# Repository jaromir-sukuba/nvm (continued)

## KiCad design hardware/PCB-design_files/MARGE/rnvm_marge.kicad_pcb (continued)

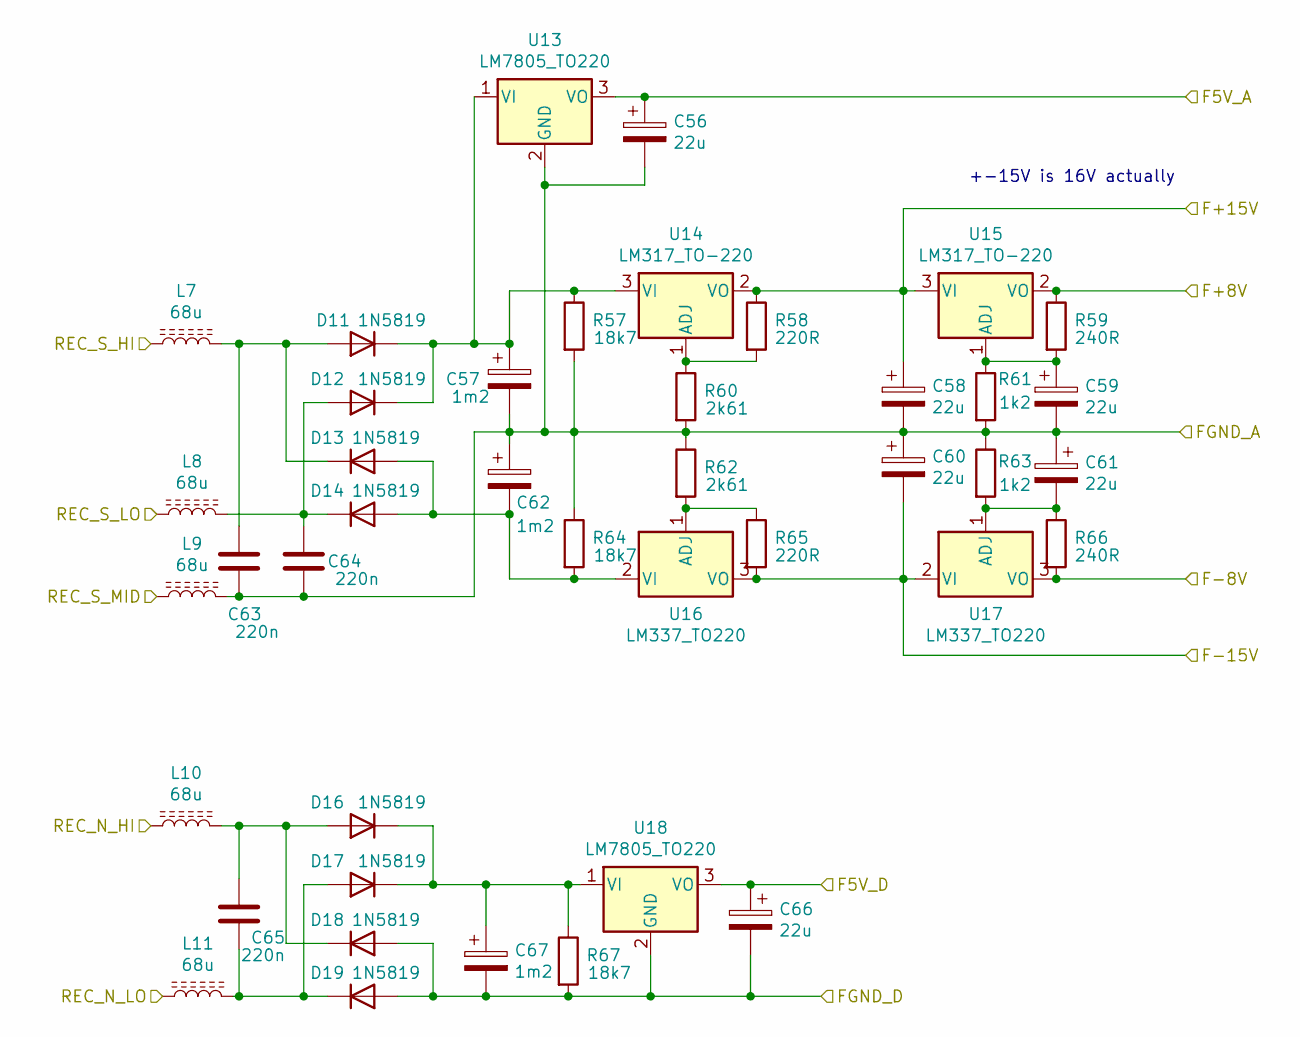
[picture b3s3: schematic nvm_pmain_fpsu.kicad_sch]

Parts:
C56, C58, C59, C60, C61, C66: 22u; CP_EIA-6032-28_Kemet-C_Pad2.25x2.35mm_HandSolder
C57, C62, C67: 1m2; CP_Radial_D12.5mm_P5.00mm
C63, C64, C65: 220n; C_0805_2012Metric_Pad1.18x1.45mm_HandSolder
D11, D12, D13, D14, D16, D17, D18, D19: 1N5819; D_MELF
L7, L8, L9, L10, L11: 68u; L_Bourns_SRN6045TA
R57, R64, R67: 18k7; R_MiniMELF_MMA-0204
R58, R65: 220R; R_MiniMELF_MMA-0204
R59, R66: 240R; R_MiniMELF_MMA-0204
R60, R62: 2k61; R_MiniMELF_MMA-0204
R61, R63: 1k2; R_MiniMELF_MMA-0204
U13, U18: LM7805_TO220; TO-220-3_Vertical
U14, U15: LM317_TO-220; TO-220-3_Vertical
U16, U17: LM337_TO220; TO-220-3_Vertical

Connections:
/nvm_pmain_fpsu/F5V_A: C56.1, U13.3 (VO); also elsewhere on the board
/nvm_pmain_fpsu/F5V_D: C66.1, U18.3 (VO); also elsewhere on the board
/nvm_pmain_fpsu/F+8V: R59.1, U15.2 (VO); also elsewhere on the board
/nvm_pmain_fpsu/F+15V: C58.1, R58.1, U14.2 (VO), U15.3 (VI); also elsewhere on the board
/nvm_pmain_fpsu/F-8V: R66.2, U17.3 (VO); also elsewhere on the board
/nvm_pmain_fpsu/F-15V: C60.2, R65.2, U16.3 (VO), U17.2 (VI); also elsewhere on the board
/nvm_pmain_fpsu/FGND_A: C56.2, C57.2, C58.2, C59.2, C60.1, C61.1, C62.1, C63.1, C64.1, L9.2, R57.2, R60.2, R61.2, R62.1, R63.1, R64.1, U13.2 (GND); also elsewhere on the board
/nvm_pmain_fpsu/FGND_D: C66.2, C67.2, D18.2 (A), D19.2 (A), R67.2, U18.2 (GND); also elsewhere on the board
/nvm_pmain_fpsu/REC_N_HI: L10.1; also elsewhere on the board
/nvm_pmain_fpsu/REC_N_LO: L11.1; also elsewhere on the board
/nvm_pmain_fpsu/REC_S_HI: L7.1; also elsewhere on the board
/nvm_pmain_fpsu/REC_S_LO: L8.1; also elsewhere on the board
/nvm_pmain_fpsu/REC_S_MID: L9.1; also elsewhere on the board
unnamed: C57.1, D11.1 (K), D12.1 (K), R57.1, U13.1 (VI), U14.3 (VI)
unnamed: C59.1, R59.2, R61.1, U15.1 (ADJ)
unnamed: C61.2, R63.2, R66.1, U17.1 (ADJ)
unnamed: C62.2, D13.2 (A), D14.2 (A), R64.2, U16.2 (VI)
unnamed: C63.2, D11.2 (A), D13.1 (K), L7.2
unnamed: C64.2, D12.2 (A), D14.1 (K), L8.2
unnamed: C65.1, D17.2 (A), D19.1 (K), L11.2
unnamed: C65.2, D16.2 (A), D18.1 (K), L10.2
unnamed: C67.1, D16.1 (K), D17.1 (K), R67.1, U18.1 (VI)
unnamed: R58.2, R60.1, U14.1 (ADJ)
unnamed: R62.2, R65.1, U16.1 (ADJ)

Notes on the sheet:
+-15V is 16V actually

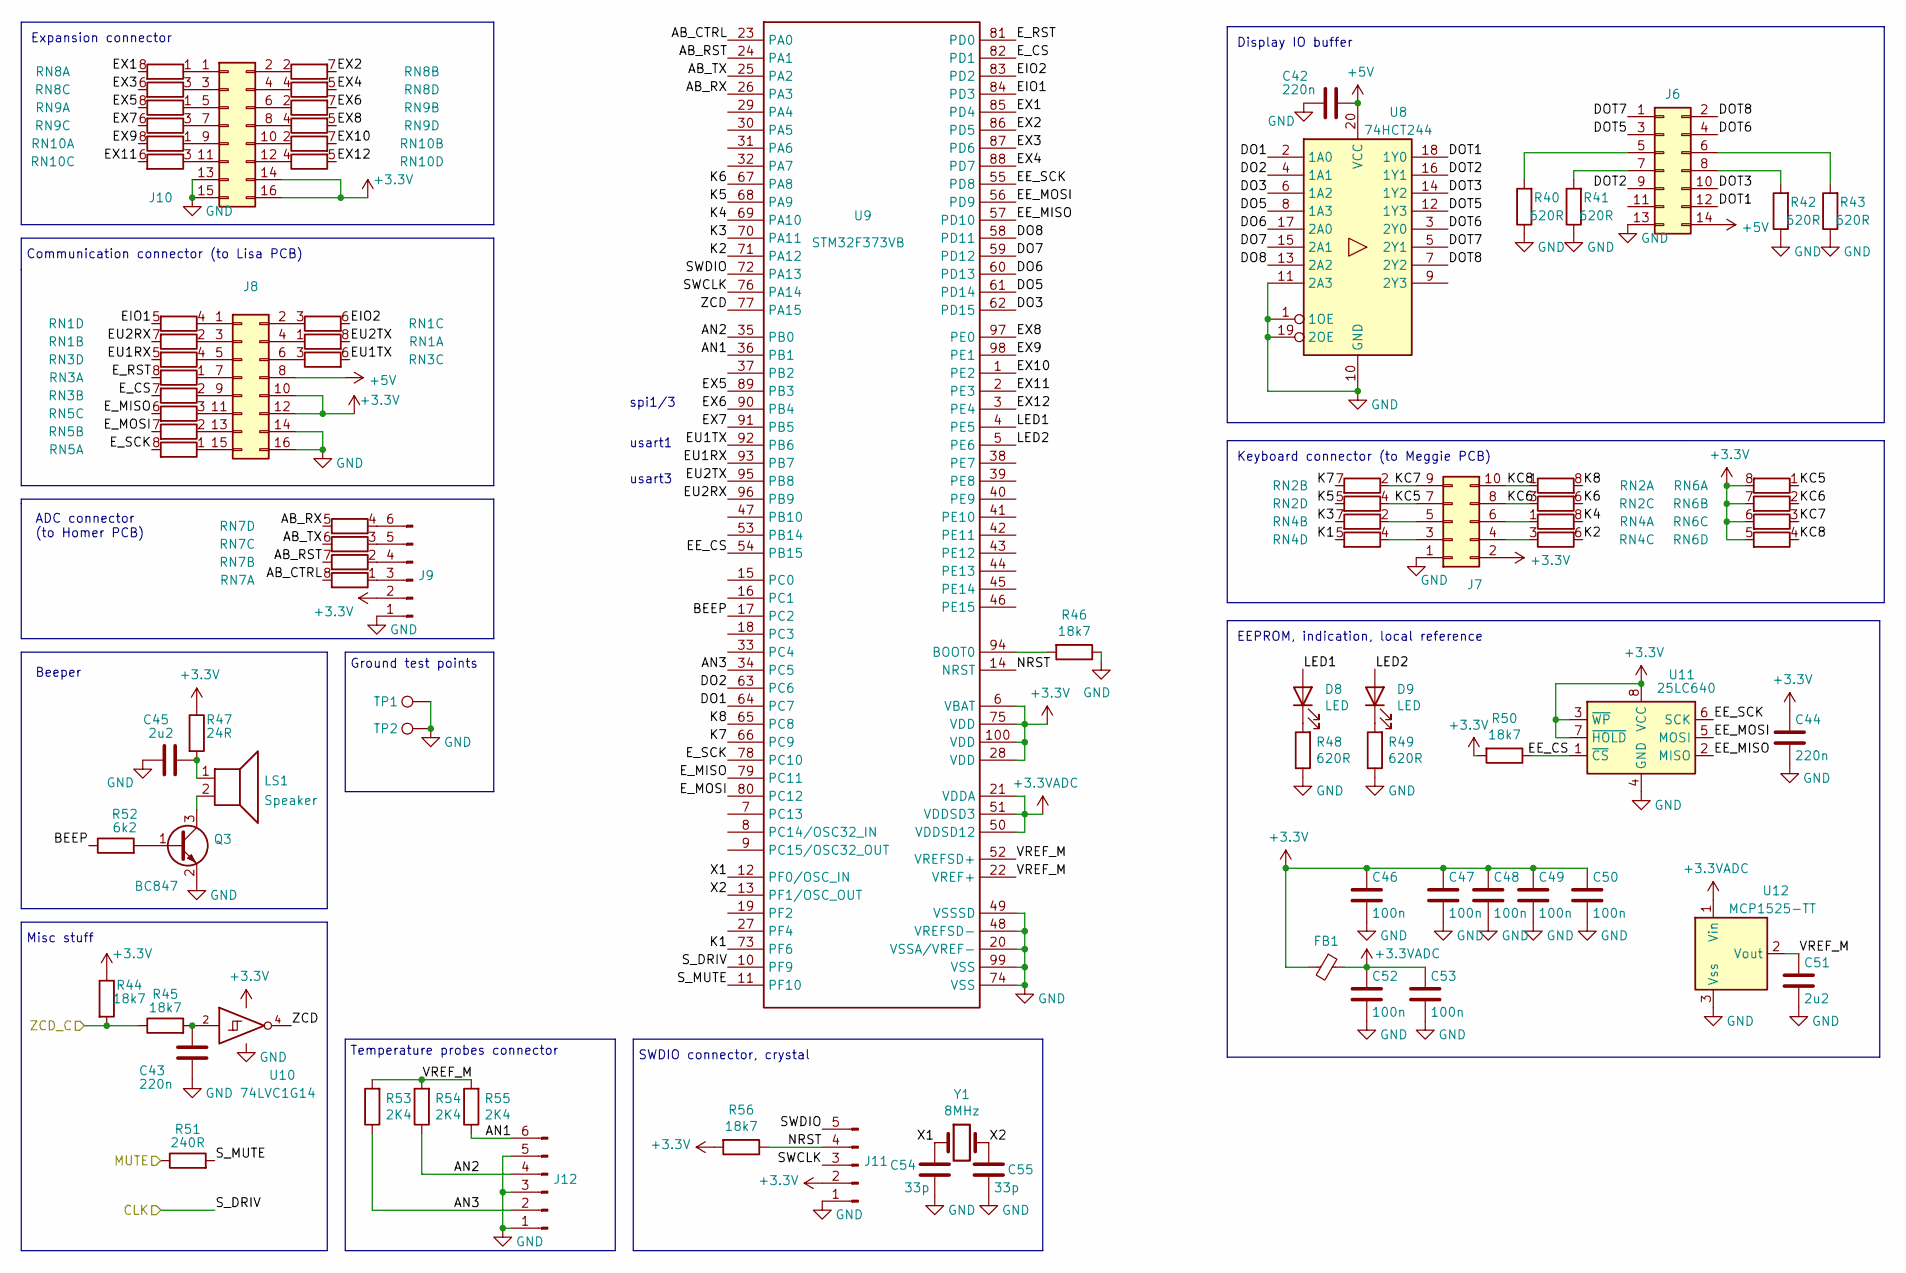
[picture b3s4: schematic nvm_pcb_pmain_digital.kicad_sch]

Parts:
C42, C43, C44: 220n; C_0805_2012Metric_Pad1.18x1.45mm_HandSolder
C45, C51: 2u2; C_0805_2012Metric_Pad1.18x1.45mm_HandSolder
C46, C47, C48, C49, C50, C52, C53: 100n; C_0603_1608Metric_Pad1.08x0.95mm_HandSolder
C54, C55: 33p; C_0805_2012Metric_Pad1.18x1.45mm_HandSolder
D8, D9: LED; LED_0805_2012Metric_Pad1.15x1.40mm_HandSolder
FB1: Ferrite_Bead_Small; L_0805_2012Metric_Pad1.05x1.20mm_HandSolder
J6: Conn_02x07_Odd_Even; IDC-Header_2x07_P2.54mm_Vertical
J7: Conn_02x05_Odd_Even; IDC-Header_2x05_P2.54mm_Vertical
J8: Conn_02x08_Odd_Even; IDC-Header_2x08_P2.54mm_Vertical
J9: Conn_01x06_Male; Molex_KK-254_AE-6410-06A_1x06_P2.54mm_Vertical
J10: Conn_02x08_Odd_Even; PinHeader_2x08_P2.54mm_Vertical
J11: Conn_01x05_Male; PinHeader_1x05_P2.54mm_Vertical
J12: Conn_01x06_Male; PinHeader_1x06_P2.54mm_Vertical
LS1: Speaker; beeper12
Q3: BC847; SOT-23
R40, R41, R42, R43, R48, R49: 620R; R_MiniMELF_MMA-0204
R44, R45, R46, R50, R56: 18k7; R_MiniMELF_MMA-0204
R47: 24R; R_MiniMELF_MMA-0204
R51: 240R; R_MiniMELF_MMA-0204
R52: 6k2; R_MiniMELF_MMA-0204
R53, R54, R55: 2K4; R_MiniMELF_MMA-0204
RN1, RN2, RN3, RN4, RN5, RN7, RN8, RN9, RN10: 51R; R_Array_Convex_4x1206
RN6: 20k; R_Array_Convex_4x1206
TP1, TP2: TestPoint; TestPoint_Loop_D3.50mm_Drill1.4mm_Beaded
U8: 74HCT244; SOIC-20W_7.5x12.8mm_P1.27mm
U9: STM32F373VB; TQFP-100_14x14mm_P0.5mm
U10: 74LVC1G14; SOT-23-5_HandSoldering
U11: 25LC640; SOIC-8_3.9x4.9mm_P1.27mm
U12: MCP1525-TT; SOT-23
Y1: 8MHz; Crystal_SMD_HC49-SD

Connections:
+3.3VADC: C52.1, C53.1, FB1.1, U9.21 (VDDA), U9.50 (VDDSD12), U9.51 (VDDSD3), U12.1 (Vin)
+3V3: C44.1, C46.1, C47.1, C48.1, C49.1, C50.1, FB1.2, J7.2, J8.10, J8.12, J9.2, J10.14, J10.16, J11.2, R44.1, R47.1, R50.2, R56.2, RN6.5 (R4.2), RN6.6 (R3.2), RN6.7 (R2.2), RN6.8 (R1.2), U9.6 (VBAT), U9.28 (VDD), U9.75 (VDD), U9.100 (VDD), U10.5 (VCC), U11.3 (~WP), U11.7 (~HOLD), U11.8 (VCC); also elsewhere on the board
+5V: C42.1, J6.14, J8.8, U8.20 (VCC); also elsewhere on the board
/nvm_pcb_pmain_digital/AB_CTRL: RN7.8 (R1.2), U9.23 (PA0)
/nvm_pcb_pmain_digital/AB_RST: RN7.7 (R2.2), U9.24 (PA1)
/nvm_pcb_pmain_digital/AB_RX: RN7.5 (R4.2), U9.26 (PA3)
/nvm_pcb_pmain_digital/AB_TX: RN7.6 (R3.2), U9.25 (PA2)
/nvm_pcb_pmain_digital/AN1: J12.6, R55.1, U9.36 (PB1)
/nvm_pcb_pmain_digital/AN2: J12.4, R54.1, U9.35 (PB0)
/nvm_pcb_pmain_digital/AN3: J12.2, R53.1, U9.34 (PC5)
/nvm_pcb_pmain_digital/BEEP: R52.1, U9.17 (PC2)
/nvm_pcb_pmain_digital/DO1: U8.2 (1A0), U9.64 (PC7)
/nvm_pcb_pmain_digital/DO2: U8.4 (1A1), U9.63 (PC6)
/nvm_pcb_pmain_digital/DO3: U8.6 (1A2), U9.62 (PD15)
/nvm_pcb_pmain_digital/DO5: U8.8 (1A3), U9.61 (PD14)
/nvm_pcb_pmain_digital/DO6: U8.17 (2A0), U9.60 (PD13)
/nvm_pcb_pmain_digital/DO7: U8.15 (2A1), U9.59 (PD12)
/nvm_pcb_pmain_digital/DO8: U8.13 (2A2), U9.58 (PD11)
/nvm_pcb_pmain_digital/DOT1: J6.12, U8.18 (1Y0)
/nvm_pcb_pmain_digital/DOT2: J6.9, U8.16 (1Y1)
/nvm_pcb_pmain_digital/DOT3: J6.10, U8.14 (1Y2)
/nvm_pcb_pmain_digital/DOT5: J6.3, U8.12 (1Y3)
/nvm_pcb_pmain_digital/DOT6: J6.4, U8.3 (2Y0)
/nvm_pcb_pmain_digital/DOT7: J6.1, U8.5 (2Y1)
/nvm_pcb_pmain_digital/DOT8: J6.2, U8.7 (2Y2)
/nvm_pcb_pmain_digital/EE_CS: R50.1, U9.54 (PB15), U11.1 (~CS)
/nvm_pcb_pmain_digital/EE_MISO: U9.57 (PD10), U11.2 (MISO)
/nvm_pcb_pmain_digital/EE_MOSI: U9.56 (PD9), U11.5 (MOSI)
/nvm_pcb_pmain_digital/EE_SCK: U9.55 (PD8), U11.6 (SCK)
/nvm_pcb_pmain_digital/EIO1: RN1.5 (R4.2), U9.84 (PD3)
/nvm_pcb_pmain_digital/EIO2: RN1.6 (R3.2), U9.83 (PD2)
/nvm_pcb_pmain_digital/EU1RX: RN3.5 (R4.2), U9.93 (PB7)
/nvm_pcb_pmain_digital/EU1TX: RN3.6 (R3.2), U9.92 (PB6)
/nvm_pcb_pmain_digital/EU2RX: RN1.7 (R2.2), U9.96 (PB9)
/nvm_pcb_pmain_digital/EU2TX: RN1.8 (R1.2), U9.95 (PB8)
/nvm_pcb_pmain_digital/EX1: RN8.8 (R1.2), U9.85 (PD4)
/nvm_pcb_pmain_digital/EX2: RN8.7 (R2.2), U9.86 (PD5)
/nvm_pcb_pmain_digital/EX3: RN8.6 (R3.2), U9.87 (PD6)
/nvm_pcb_pmain_digital/EX4: RN8.5 (R4.2), U9.88 (PD7)
/nvm_pcb_pmain_digital/EX5: RN9.8 (R1.2), U9.89 (PB3)
/nvm_pcb_pmain_digital/EX6: RN9.7 (R2.2), U9.90 (PB4)
/nvm_pcb_pmain_digital/EX7: RN9.6 (R3.2), U9.91 (PB5)
/nvm_pcb_pmain_digital/EX8: RN9.5 (R4.2), U9.97 (PE0)
/nvm_pcb_pmain_digital/EX9: RN10.8 (R1.2), U9.98 (PE1)
/nvm_pcb_pmain_digital/EX10: RN10.7 (R2.2), U9.1 (PE2)
/nvm_pcb_pmain_digital/EX11: RN10.6 (R3.2), U9.2 (PE3)
/nvm_pcb_pmain_digital/EX12: RN10.5 (R4.2), U9.3 (PE4)
/nvm_pcb_pmain_digital/E_CS: RN3.7 (R2.2), U9.82 (PD1)
/nvm_pcb_pmain_digital/E_MISO: RN5.6 (R3.2), U9.79 (PC11)
/nvm_pcb_pmain_digital/E_MOSI: RN5.7 (R2.2), U9.80 (PC12)
/nvm_pcb_pmain_digital/E_RST: RN3.8 (R1.2), U9.81 (PD0)
/nvm_pcb_pmain_digital/E_SCK: RN5.8 (R1.2), U9.78 (PC10)
/nvm_pcb_pmain_digital/K1: RN4.5 (R4.2), U9.73 (PF6)
/nvm_pcb_pmain_digital/K2: RN4.6 (R3.2), U9.71 (PA12)
/nvm_pcb_pmain_digital/K3: RN4.7 (R2.2), U9.70 (PA11)
/nvm_pcb_pmain_digital/K4: RN4.8 (R1.2), U9.69 (PA10)
/nvm_pcb_pmain_digital/K5: RN2.5 (R4.2), U9.68 (PA9)
/nvm_pcb_pmain_digital/K6: RN2.6 (R3.2), U9.67 (PA8)
/nvm_pcb_pmain_digital/K7: RN2.7 (R2.2), U9.66 (PC9)
/nvm_pcb_pmain_digital/K8: RN2.8 (R1.2), U9.65 (PC8)
/nvm_pcb_pmain_digital/KC5: J7.7, RN2.4 (R4.1), RN6.1 (R1.1)
/nvm_pcb_pmain_digital/KC6: J7.8, RN2.3 (R3.1), RN6.2 (R2.1)
/nvm_pcb_pmain_digital/KC7: J7.9, RN2.2 (R2.1), RN6.3 (R3.1)
/nvm_pcb_pmain_digital/KC8: J7.10, RN2.1 (R1.1), RN6.4 (R4.1)
/nvm_pcb_pmain_digital/LED1: D8.2 (A), U9.4 (PE5)
/nvm_pcb_pmain_digital/LED2: D9.2 (A), U9.5 (PE6)
/nvm_pcb_pmain_digital/MUTE: R51.1; also elsewhere on the board
/nvm_pcb_pmain_digital/NRST: J11.4, R56.1, U9.14 (NRST)
/nvm_pcb_pmain_digital/SWCLK: J11.3, U9.76 (PA14)
/nvm_pcb_pmain_digital/SWDIO: J11.5, U9.72 (PA13)
/nvm_pcb_pmain_digital/S_DRIV: U9.10 (PF9); also elsewhere on the board
/nvm_pcb_pmain_digital/S_MUTE: R51.2, U9.11 (PF10)
/nvm_pcb_pmain_digital/VREF_M: C51.1, R53.2, R54.2, R55.2, U9.22 (VREF+), U9.52 (VREFSD+), U12.2 (Vout)
/nvm_pcb_pmain_digital/X1: C54.1, U9.12 (PF0/OSC_IN), Y1.1
/nvm_pcb_pmain_digital/X2: C55.1, U9.13 (PF1/OSC_OUT), Y1.2
/nvm_pcb_pmain_digital/ZCD: U9.77 (PA15), U10.4
/nvm_pcb_pmain_digital/ZCD_C: R44.2, R45.1; also elsewhere on the board
GND: C42.2, C43.2, C44.2, C45.1, C46.2, C47.2, C48.2, C49.2, C50.2, C51.2, C52.2, C53.2, C54.2, C55.2, J6.13, J7.1, J8.14, J8.16, J9.1, J10.13, J10.15, J11.1, J12.1, J12.3, J12.5, Q3.2 (E), R40.1, R41.1, R42.1, R43.1, R46.1, R48.1, R49.1, TP1.1, TP2.1, U8.1 (1OE), U8.10 (GND), U8.11 (2A3), U8.19 (2OE), U9.20 (VSSA/VREF-), U9.48 (VREFSD-), U9.49 (VSSSD), U9.74 (VSS), U9.99 (VSS), U10.3 (GND), U11.4 (GND), U12.3 (Vss); also elsewhere on the board
unnamed: C43.1, R45.2, U10.2
unnamed: C45.2, LS1.1, R47.2
unnamed: D8.1 (K), R48.2
unnamed: D9.1 (K), R49.2
unnamed: J6.5, R40.2
unnamed: J6.6, R43.2
unnamed: J6.7, R41.2
unnamed: J6.8, R42.2
unnamed: J7.3, RN4.4 (R4.1)
unnamed: J7.4, RN4.3 (R3.1)
unnamed: J7.5, RN4.2 (R2.1)
unnamed: J7.6, RN4.1 (R1.1)
unnamed: J8.1, RN1.4 (R4.1)
unnamed: J8.2, RN1.3 (R3.1)
unnamed: J8.3, RN1.2 (R2.1)
unnamed: J8.4, RN1.1 (R1.1)
unnamed: J8.5, RN3.4 (R4.1)
unnamed: J8.6, RN3.3 (R3.1)
unnamed: J8.7, RN3.1 (R1.1)
unnamed: J8.9, RN3.2 (R2.1)
unnamed: J8.11, RN5.3 (R3.1)
unnamed: J8.13, RN5.2 (R2.1)
unnamed: J8.15, RN5.1 (R1.1)
unnamed: J9.3, RN7.1 (R1.1)
unnamed: J9.4, RN7.2 (R2.1)
unnamed: J9.5, RN7.3 (R3.1)
unnamed: J9.6, RN7.4 (R4.1)
unnamed: J10.1, RN8.1 (R1.1)
unnamed: J10.2, RN8.2 (R2.1)
unnamed: J10.3, RN8.3 (R3.1)
unnamed: J10.4, RN8.4 (R4.1)
unnamed: J10.5, RN9.1 (R1.1)
unnamed: J10.6, RN9.2 (R2.1)
unnamed: J10.7, RN9.3 (R3.1)
unnamed: J10.8, RN9.4 (R4.1)
unnamed: J10.9, RN10.1 (R1.1)
unnamed: J10.10, RN10.2 (R2.1)
unnamed: J10.11, RN10.3 (R3.1)
unnamed: J10.12, RN10.4 (R4.1)
unnamed: LS1.2, Q3.3 (C)
unnamed: Q3.1 (B), R52.2
unnamed: R46.2, U9.94 (BOOT0)

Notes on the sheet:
Beeper
Expansion connector
Temperature probes connector
SWDIO connector, crystal
Communication connector (to Lisa PCB)
Ground test points
ADC connector (to Homer PCB)
Keyboard connector (to Meggie PCB)
spi1/3
usart3
Display IO buffer
usart1
EEPROM, indication, local reference
Misc stuff

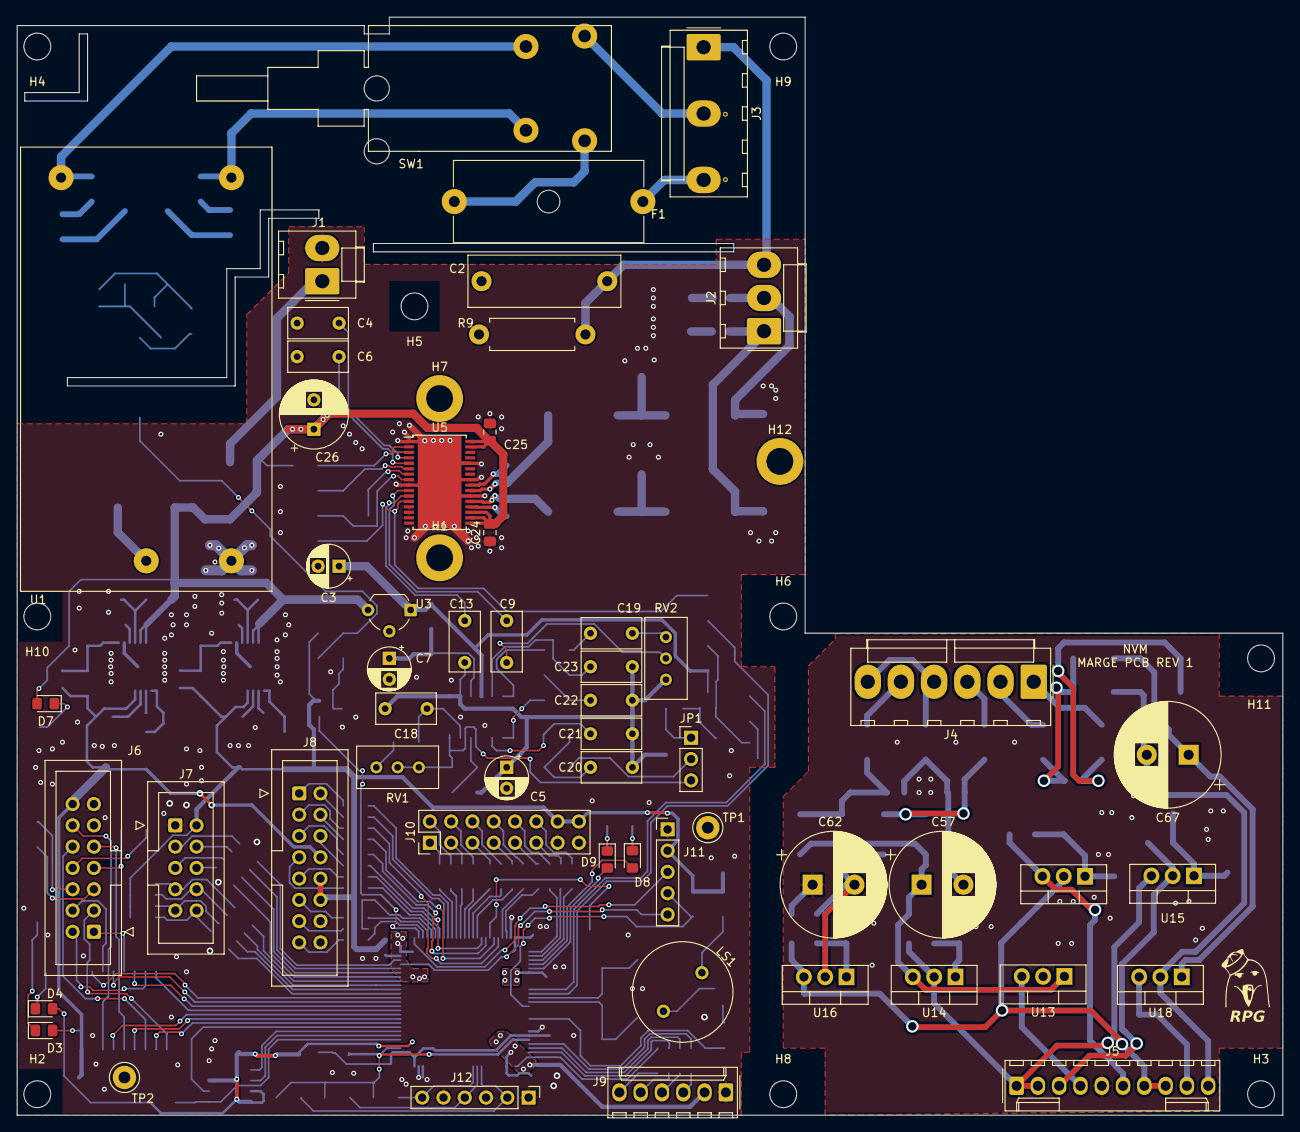
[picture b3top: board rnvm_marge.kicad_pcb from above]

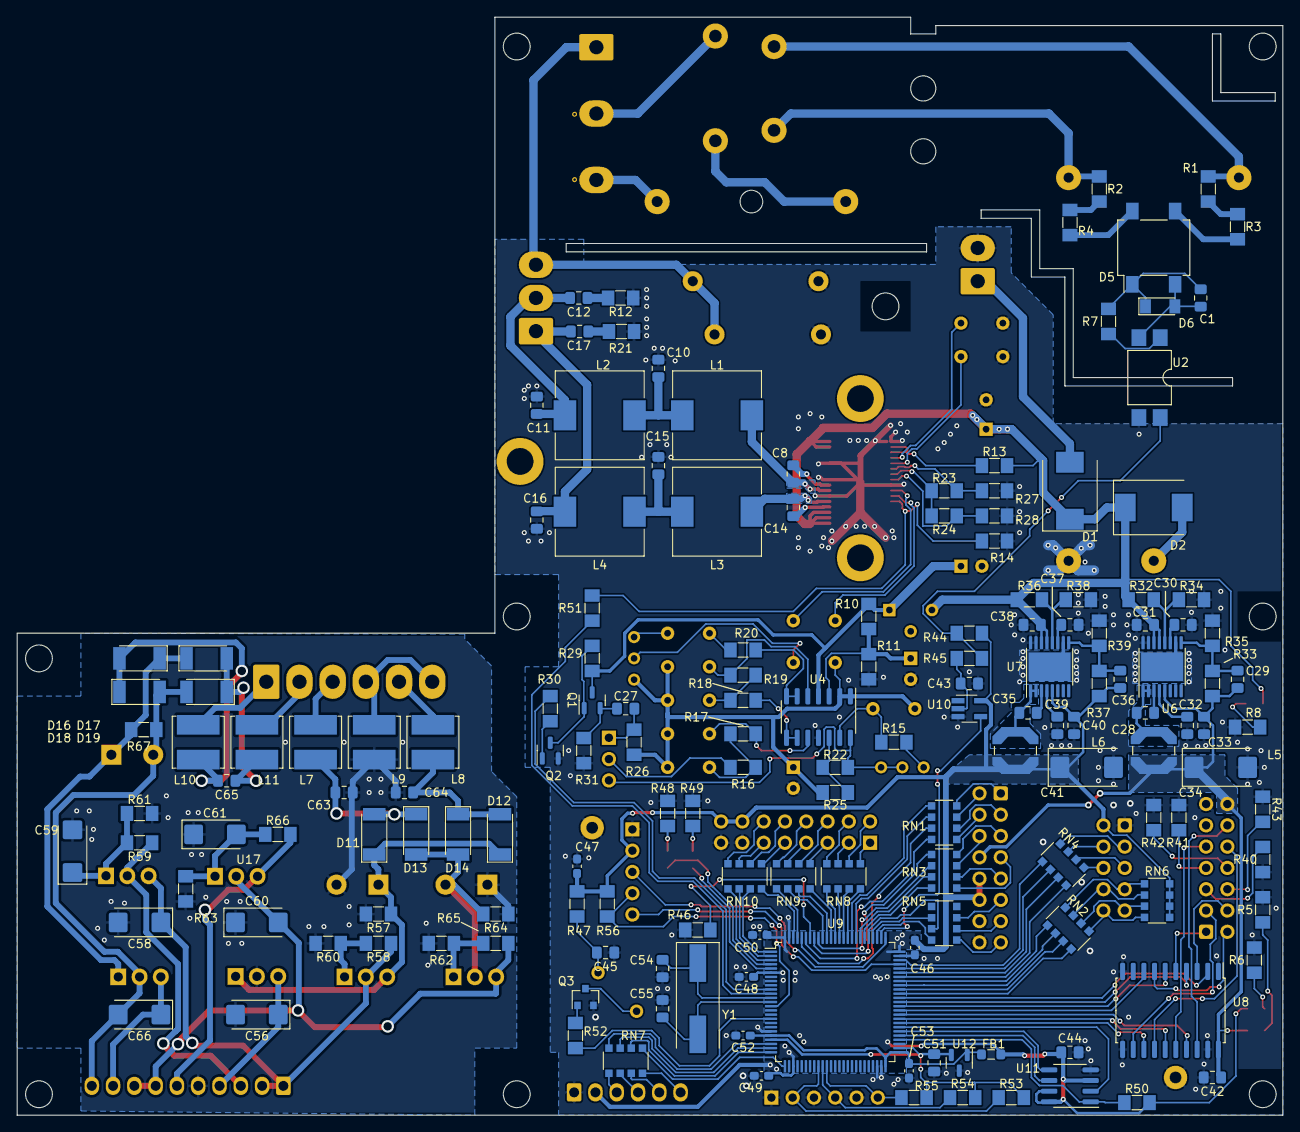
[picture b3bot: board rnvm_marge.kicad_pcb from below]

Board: 2 copper layers, 151.0 x 131.0 mm, 228 parts (160 on the bottom side), 214 nets.

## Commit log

2022-05-15 readme update
2022-05-16 readme
2022-05-16 BOM moved into correct directory, readme update
2022-05-18 Typo fix
2022-05-19 Corrected and rewritten
2022-05-19 added test data
2022-05-19 added measurement data
